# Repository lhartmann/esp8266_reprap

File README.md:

#ESP8266 I2S 32bit Realtime Shift Register Driver 

I believe I found a way to use just an ESP8266 module to control a set of 3D printer stepper drivers directly. This code demonstrates how.

Background:

1.  Other projects show how to use ESP01 as a wifi-serial bridge to the arduinos, but serial is still a bottleneck and wifi uploads are impractical.
2.  Altough ESP8266 does 160MHz at 32bits processing (versus 16MHZ 8-bit from most Arduinos) it has insufficient realtime GPIO for controlling printers.
3.  Raspberry pi shared the realtime gpio limitation, but wallacoloo still did reprap control using DMA. Nice! https://www.youtube.com/watch?v=g4UD5MRas3E
4.  CNLohr did a really cool WS2812 led driver (weird one-wire serial protocol) using ESP8266 I2S audio output and DMA. https://www.youtube.com/watch?v=6zqGwxqJQnw
5.  I2S and SPI look very much alike, and SPI can control shift registers. Hey! Opportunity!

I got the code from CNLohr on github, modified it to output a 32 bit counter (16 bit left + 16 bit right channels) via a circular DMA buffer, and created a small PCB with four cascaded 74HC595 shift registers. wiring is simple:
- I2S Data to '595 input data
- I2S Bitclock to '595 shift clock
- I2s word clock (left/right) to '595 buffer clock.

This is what RAW I2S output signals for the counter look like: word-clock (yellow), bit clock (cyan), data (purple). Notice how LSB of data is output after the word clock rising edge.

Fixed the offset (software shifing) to match the parallel outputs, raised the frequency a bit (just cause), plugged in the shifter board. Now this is what word-clock (yellow) and the 3LSBs (cyan=1, purple=2, blue=4) look like:

The code and the PCB: (https://github.com/lhartmann/esp8266_reprap)

What this does:

- Allows realtime bitbanging of 32 data bits via I2S and DMA.
- Demo code just outputs a 32bit counter at 185kHz sample rate.
- Reference shifter board is provided.

Limitations:

- 1MSB is actually delayed by 1 sample due to I2S signaling standard. This delay is constant so it could be compensated, but I didn't bother.

Hopes for the future: RepRap 3D Printing.

- No extra arduino necessary, ESP would control the drivers directly.
- SDcard uploads over wifi would be feasible for large files, no more serial connection bottleneck with wifi-serial bridging. 
- Browser-side slicing with slic3r and (http://www.skulpt.org). No software install required on the client!

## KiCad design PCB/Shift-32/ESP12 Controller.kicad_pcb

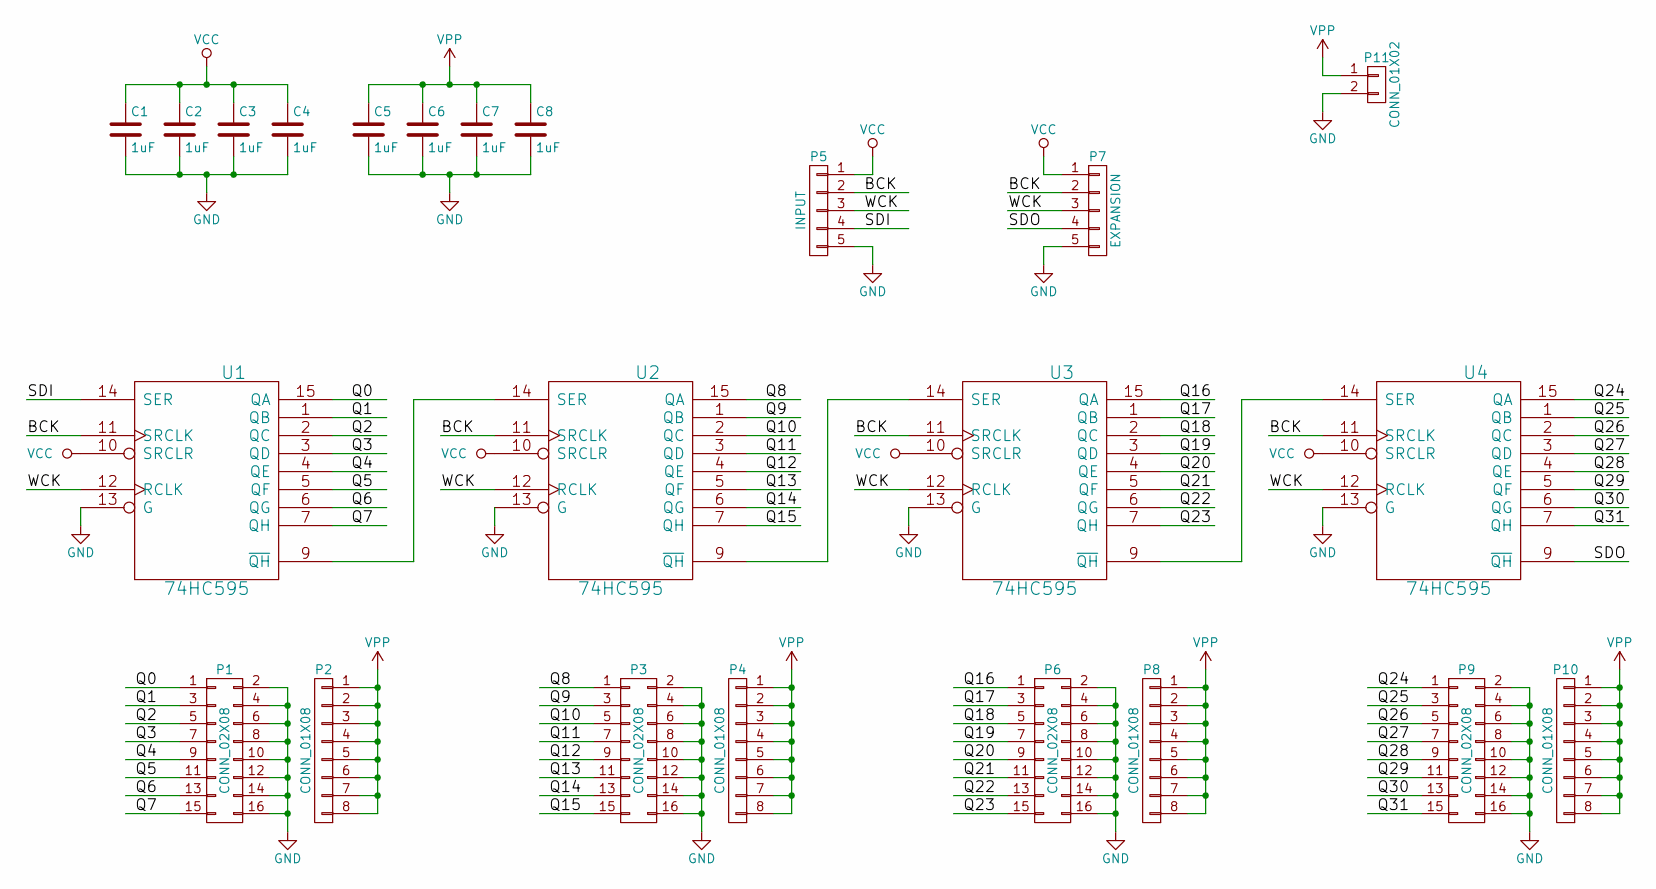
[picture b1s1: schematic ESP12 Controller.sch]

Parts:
C1, C2, C3, C4, C5, C6, C7, C8: 1uF; C_0805_HandSoldering
P1, P3, P6, P9: CONN_02X08; Socket_Strip_Straight_2x08
P2, P4, P8, P10: CONN_01X08; Socket_Strip_Straight_1x08
P5: INPUT; Socket_Strip_Straight_1x05
P7: EXPANSION; Socket_Strip_Straight_1x05
P11: CONN_01X02; Socket_Strip_Straight_1x02
U1, U2, U3, U4: 74HC595; SO-16-N

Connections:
/BCK: P5.2, P7.2, U1.11 (SRCLK), U2.11 (SRCLK), U3.11 (SRCLK), U4.11 (SRCLK)
/Q0: P1.1, U1.15 (QA)
/Q1: P1.3, U1.1 (QB)
/Q2: P1.5, U1.2 (QC)
/Q3: P1.7, U1.3 (QD)
/Q4: P1.9, U1.4 (QE)
/Q5: P1.11, U1.5 (QF)
/Q6: P1.13, U1.6 (QG)
/Q7: P1.15, U1.7 (QH)
/Q8: P3.1, U2.15 (QA)
/Q9: P3.3, U2.1 (QB)
/Q10: P3.5, U2.2 (QC)
/Q11: P3.7, U2.3 (QD)
/Q12: P3.9, U2.4 (QE)
/Q13: P3.11, U2.5 (QF)
/Q14: P3.13, U2.6 (QG)
/Q15: P3.15, U2.7 (QH)
/Q16: P6.1, U3.15 (QA)
/Q17: P6.3, U3.1 (QB)
/Q18: P6.5, U3.2 (QC)
/Q19: P6.7, U3.3 (QD)
/Q20: P6.9, U3.4 (QE)
/Q21: P6.11, U3.5 (QF)
/Q22: P6.13, U3.6 (QG)
/Q23: P6.15, U3.7 (QH)
/Q24: P9.1, U4.15 (QA)
/Q25: P9.3, U4.1 (QB)
/Q26: P9.5, U4.2 (QC)
/Q27: P9.7, U4.3 (QD)
/Q28: P9.9, U4.4 (QE)
/Q29: P9.11, U4.5 (QF)
/Q30: P9.13, U4.6 (QG)
/Q31: P9.15, U4.7 (QH)
/SDI: P5.4, U1.14 (SER)
/SDO: P7.4, U4.9 (~QH)
/WCK: P5.3, P7.3, U1.12 (RCLK), U2.12 (RCLK), U3.12 (RCLK), U4.12 (RCLK)
GND: C1.2, C2.2, C3.2, C4.2, C5.2, C6.2, C7.2, C8.2, P1.2, P1.4, P1.6, P1.8, P1.10, P1.12, P1.14, P1.16, P3.2, P3.4, P3.6, P3.8, P3.10, P3.12, P3.14, P3.16, P5.5, P6.2, P6.4, P6.6, P6.8, P6.10, P6.12, P6.14, P6.16, P7.5, P9.2, P9.4, P9.6, P9.8, P9.10, P9.12, P9.14, P9.16, P11.2, U1.8 (GND), U1.13 (G), U2.8 (GND), U2.13 (G), U3.8 (GND), U3.13 (G), U4.8 (GND), U4.13 (G)
unnamed: U1.9 (~QH), U2.14 (SER)
unnamed: U2.9 (~QH), U3.14 (SER)
unnamed: U3.9 (~QH), U4.14 (SER)
VCC: C1.1, C2.1, C3.1, C4.1, P5.1, P7.1, U1.10 (SRCLR), U1.16 (VCC), U2.10 (SRCLR), U2.16 (VCC), U3.10 (SRCLR), U3.16 (VCC), U4.10 (SRCLR), U4.16 (VCC)
VPP: C5.1, C6.1, C7.1, C8.1, P2.1, P2.2, P2.3, P2.4, P2.5, P2.6, P2.7, P2.8, P4.1, P4.2, P4.3, P4.4, P4.5, P4.6, P4.7, P4.8, P8.1, P8.2, P8.3, P8.4, P8.5, P8.6, P8.7, P8.8, P10.1, P10.2, P10.3, P10.4, P10.5, P10.6, P10.7, P10.8, P11.1

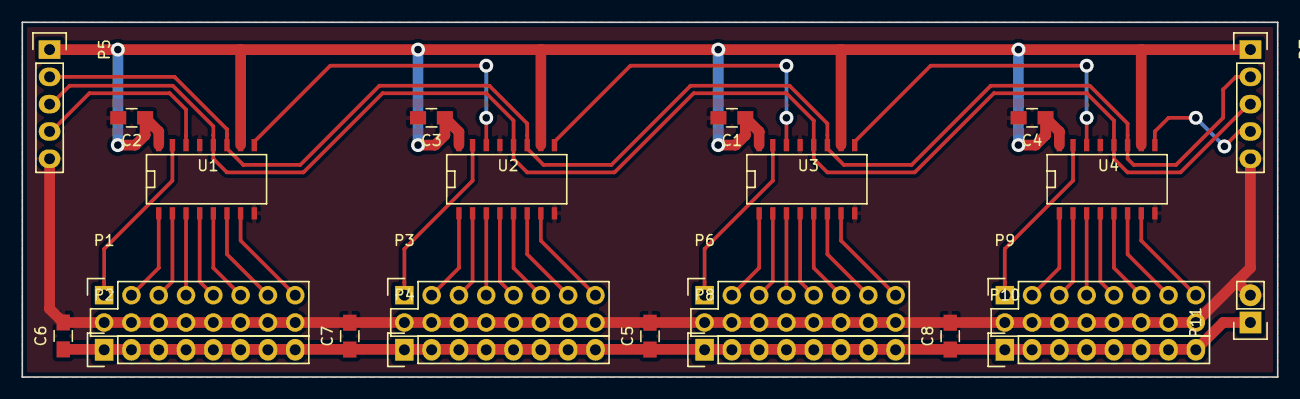
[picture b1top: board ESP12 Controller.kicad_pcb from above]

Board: 2 copper layers, 116.8 x 33.0 mm, 23 parts (0 on the bottom side), 42 nets.

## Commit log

2015-12-10 Modified to drive four 74HC595 as 32bit continuous realtime counter.
2015-12-10 Added reference shifter PCB.
2015-12-10 Updated documentation.
